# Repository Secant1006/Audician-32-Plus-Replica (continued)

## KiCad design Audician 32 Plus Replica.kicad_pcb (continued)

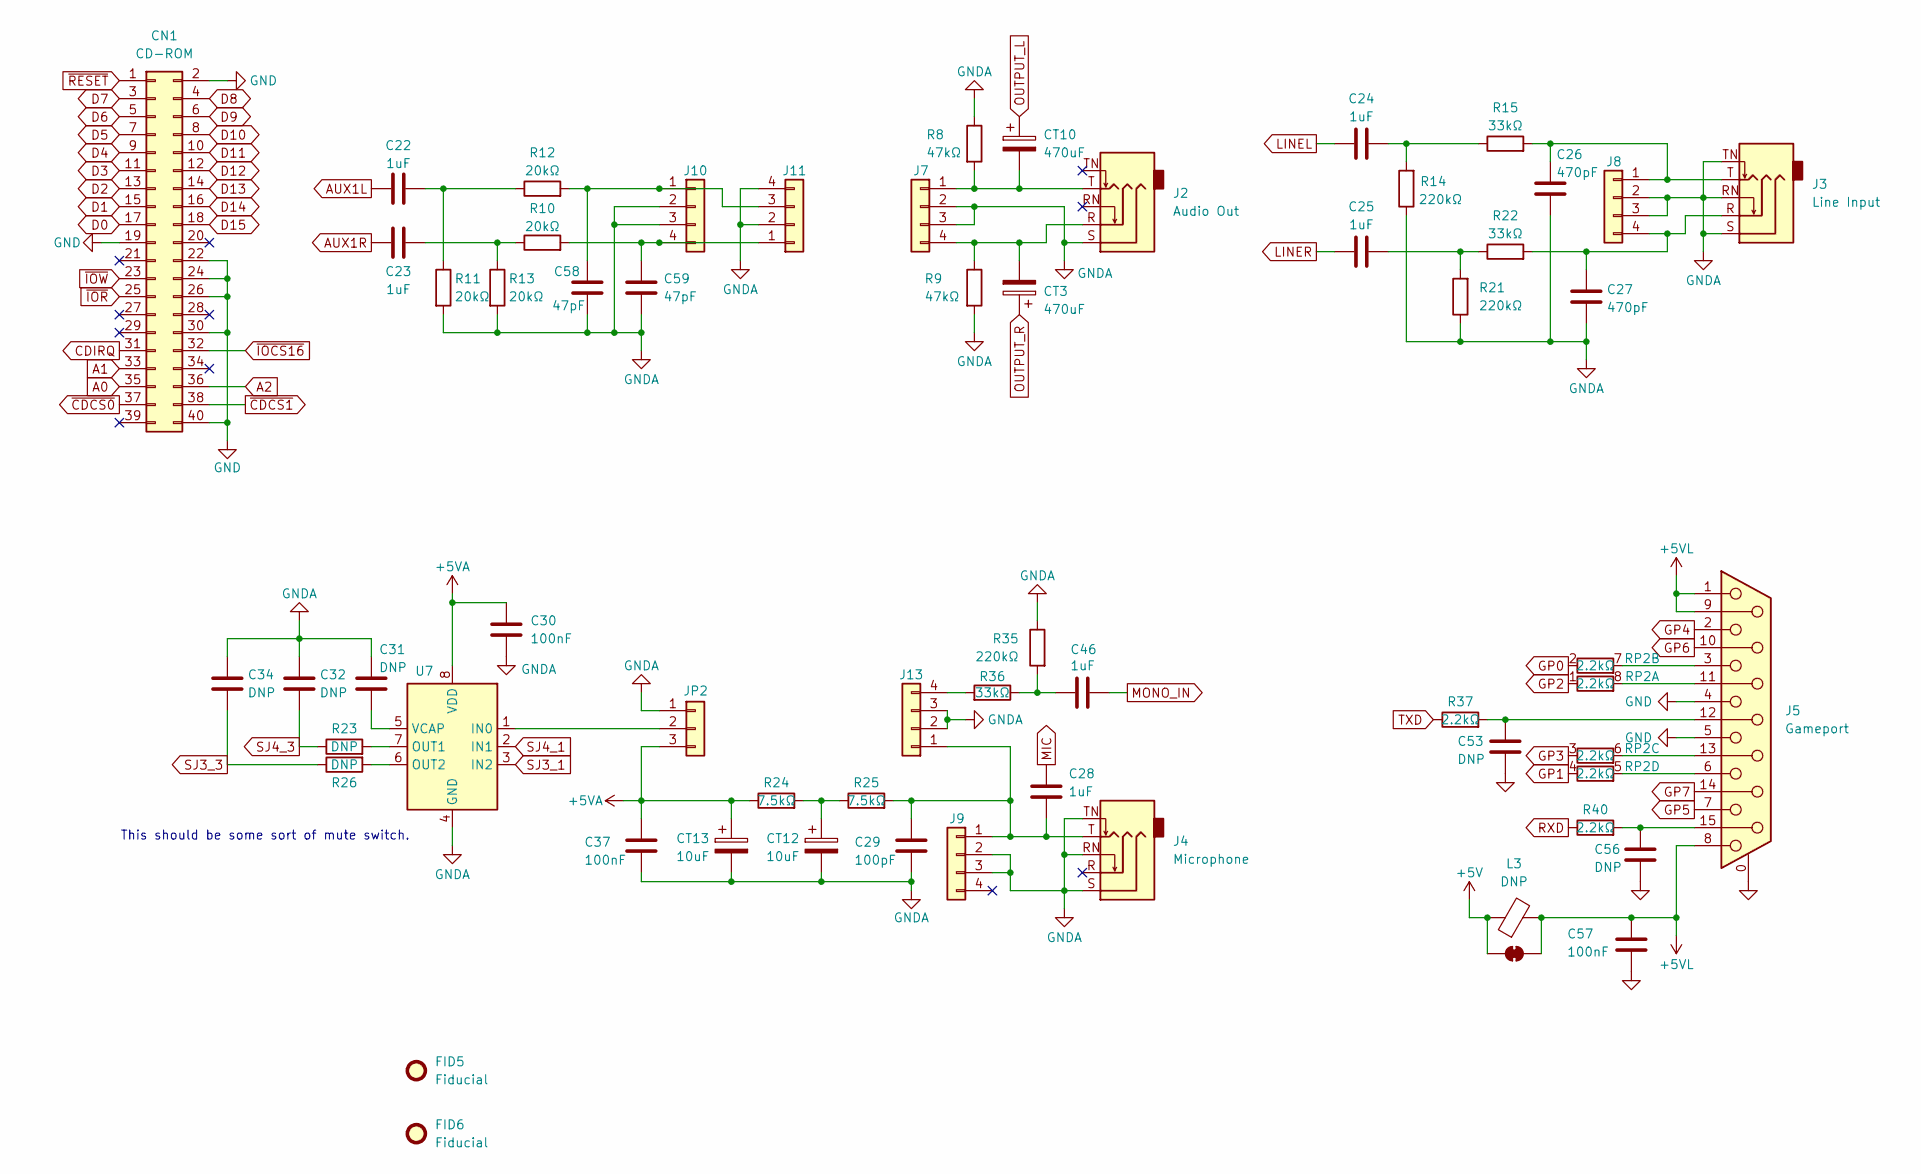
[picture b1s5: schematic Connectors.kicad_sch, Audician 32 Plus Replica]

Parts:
C22, C23, C24, C25, C28, C46: 1uF; C_0805_2012Metric; LCSC C28323
C26, C27: 470pF; C_0805_2012Metric; LCSC C1743
C29: 100pF; C_0805_2012Metric; LCSC C1790
C30, C57: 100nF; C_0805_2012Metric
C31, C32, C34, C53, C56: DNP; C_0805_2012Metric
C37: 100nF; C_0805_2012Metric; LCSC C49678
C58, C59: 47pF; C_0805_2012Metric; LCSC C14857
CN1: CD-ROM; IDC-Header_2x20_P2.54mm_Vertical
CT3, CT10: 470uF; CP_Radial_D8.0mm_P3.50mm; LCSC C106735
CT12, CT13: 10uF; CP_Radial_D5.0mm_P2.50mm; LCSC C5123345
FID5, FID6: Fiducial; Fiducial_0.75mm_Mask1.5mm
J2: Audio Out; Jack_3.5mm_PJ-317_Horizontal; LCSC C381121
J3: Line Input; Jack_3.5mm_PJ-317_Horizontal; LCSC C381121
J4: Microphone; Jack_3.5mm_PJ-317_Horizontal; LCSC C381121
J5: Gameport; DSUB-15_Socket_Horizontal_P2.77x2.84mm_EdgePinOffset7.70mm_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; LCSC C77835
J7, J8, J9: Conn_01x04; PinHeader_1x04_P2.54mm_Vertical
J10: Conn_01x04; PinHeader_1x04_P2.54mm_Vertical; LCSC C2691448
J11, J13: Conn_01x04; JST_PH_B4B-PH-K_1x04_P2.00mm_Vertical_Reversed; LCSC C722763
JP2: Conn_01x03; PinHeader_1x03_P2.54mm_Vertical
L3: DNP; L_Axial_L7.0mm_D3.3mm_P10.16mm_Horizontal_Fastron_MICC
R8, R9: 47kΩ; R_0805_2012Metric; LCSC C17713
R10, R11, R12, R13: 20kΩ; R_0805_2012Metric; LCSC C4328
R14, R21, R35: 220kΩ; R_0805_2012Metric; LCSC C17556
R15, R22, R36: 33kΩ; R_0805_2012Metric; LCSC C17633
R23, R26: DNP; R_0805_2012Metric
R24, R25: 7.5kΩ; R_0805_2012Metric; LCSC C17807
R37, R40: 2.2kΩ; R_0805_2012Metric; LCSC C17520
RP2: 2.2kΩ; R_Array_Convex_4x0603; LCSC C52175185
SJL3: SolderJumper_2_Bridged; SolderJumper-2_P1.3mm_Bridged_RoundedPad1.0x1.5mm
U7: Mysterious Chip; SOIC-8_3.9x4.9mm_P1.27mm

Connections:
+5V: L3.1, SJL3.1 (A); also elsewhere on the board
+5VA: C30.1, C37.1, CT13.1, JP2.3, R24.1, U7.8 (VDD); also elsewhere on the board
+5VL: C57.1, J5.1, J5.8, J5.9, L3.2, SJL3.2 (B)
A0: CN1.35; also elsewhere on the board
A1: CN1.33; also elsewhere on the board
A2: CN1.36; also elsewhere on the board
AUX1L: C22.1; also elsewhere on the board
AUX1R: C23.1; also elsewhere on the board
CDIRQ: CN1.31; also elsewhere on the board
D0: CN1.17; also elsewhere on the board
D1: CN1.15; also elsewhere on the board
D2: CN1.13; also elsewhere on the board
D3: CN1.11; also elsewhere on the board
D4: CN1.9; also elsewhere on the board
D5: CN1.7; also elsewhere on the board
D6: CN1.5; also elsewhere on the board
D7: CN1.3; also elsewhere on the board
D8: CN1.4; also elsewhere on the board
D9: CN1.6; also elsewhere on the board
D10: CN1.8; also elsewhere on the board
D11: CN1.10; also elsewhere on the board
D12: CN1.12; also elsewhere on the board
D13: CN1.14; also elsewhere on the board
D14: CN1.16; also elsewhere on the board
D15: CN1.18; also elsewhere on the board
GND: C53.2, C56.2, C57.2, CN1.2, CN1.19, CN1.22, CN1.24, CN1.26, CN1.30, CN1.40, J5.0 (PAD), J5.4, J5.5; also elsewhere on the board
GNDA: C26.2, C27.2, C29.2, C30.2, C31.1, C32.1, C34.1, C37.2, C58.2, C59.2, CT12.2, CT13.2, J2.S, J3.RN, J3.S, J3.TN, J4.RN, J4.S, J4.TN, J7.2, J7.3, J8.2, J8.3, J9.2, J9.3, J10.2, J10.3, J11.2, J11.4, J13.2, J13.3, JP2.1, R8.1, R9.2, R11.2, R13.2, R14.1, R21.1, R35.1, U7.4 (GND); also elsewhere on the board
GP0: RP2.2 (R2.1); also elsewhere on the board
GP1: RP2.4 (R4.1); also elsewhere on the board
GP2: RP2.1 (R1.1); also elsewhere on the board
GP3: RP2.3 (R3.1); also elsewhere on the board
GP4: J5.2; also elsewhere on the board
GP5: J5.7; also elsewhere on the board
GP6: J5.10; also elsewhere on the board
GP7: J5.14; also elsewhere on the board
LINEL: C24.1; also elsewhere on the board
LINER: C25.1; also elsewhere on the board
MIC: C28.1; also elsewhere on the board
MONO_IN: C46.2; also elsewhere on the board
unnamed: C22.2, R11.1, R12.1
unnamed: C23.2, R10.1, R13.1
unnamed: C24.2, R14.2, R15.1
unnamed: C25.2, R21.2, R22.1
unnamed: C46.1, R35.2, R36.1
unnamed: CT12.1, R24.2, R25.1
unnamed: C53.1, J5.12, R37.2
unnamed: J5.13, RP2.6 (R3.2)
unnamed: C56.1, J5.15, R40.2
unnamed: J5.11 (P111), RP2.8 (R1.2)
unnamed: CT10.2, J2.T, J7.1, R8.2
unnamed: CT3.2, J2.R, J7.4, R9.1
unnamed: C26.1, J3.T, J8.1, R15.2
unnamed: C27.1, J3.R, J8.4, R22.2
unnamed: C58.1, J10.1, J11.3, R12.2
unnamed: C59.1, J10.4, J11.1, R10.2
unnamed: C28.2, C29.1, J4.T, J9.1, J13.1, R25.2
unnamed: J13.4, R36.2
unnamed: JP2.2, U7.1 (IN0)
unnamed: J5.3, RP2.7 (R2.2)
unnamed: J5.6, RP2.5 (R4.2)
unnamed: R23.2, U7.7 (OUT1)
unnamed: R26.2, U7.6 (OUT2)
unnamed: C31.2, U7.5 (VCAP)
OUTPUT_L: CT10.1; also elsewhere on the board
OUTPUT_R: CT3.1; also elsewhere on the board
RXD: R40.1; also elsewhere on the board
SJ3_1: U7.3 (IN2); also elsewhere on the board
SJ3_3: C34.2, R26.1; also elsewhere on the board
SJ4_1: U7.2 (IN1); also elsewhere on the board
SJ4_3: C32.2, R23.1; also elsewhere on the board
TXD: R37.1; also elsewhere on the board
~CDCS0: CN1.37; also elsewhere on the board
~CDCS1: CN1.38; also elsewhere on the board
~IOCS16: CN1.32; also elsewhere on the board
~IOR: CN1.25; also elsewhere on the board
~IOW: CN1.23; also elsewhere on the board
~RESET: CN1.1; also elsewhere on the board

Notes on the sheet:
This should be some sort of mute switch.

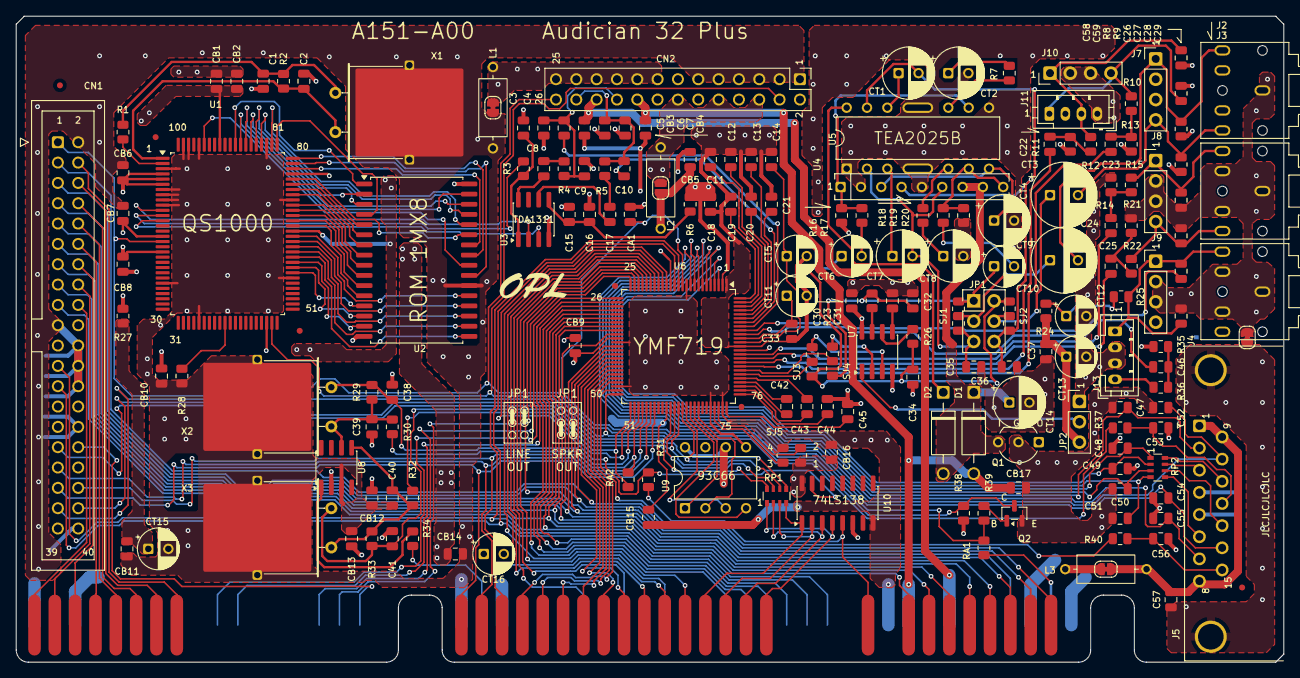
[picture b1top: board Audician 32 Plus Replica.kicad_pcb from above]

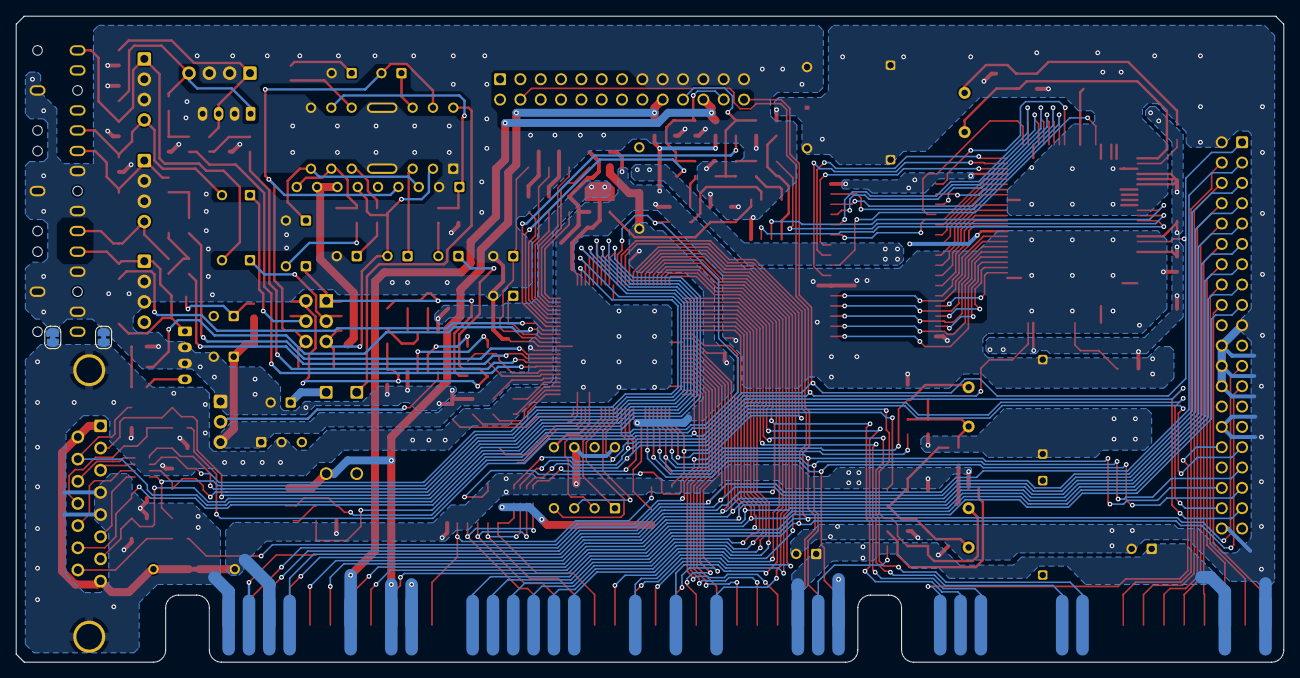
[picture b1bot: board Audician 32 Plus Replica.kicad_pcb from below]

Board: 2 copper layers, 158.4 x 80.7 mm, 189 parts (2 on the bottom side), 203 nets.
